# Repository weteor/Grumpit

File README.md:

### Grump'it

Grumpish 28 key BLE split keyboard 

## features

- Hotswap sockets (Choc V2)
- Seeed Xiao Controller (w/ ZMK firmware)
- gerber and case files (kicad files, stl as well as freecad files)
- Bluetooth (w/ Xiao BLE)
- completely open source, permissive license ([CERN-OHL-P](https://cern-ohl.web.cern.ch/home))

## want one?

All production files you need to build your own board can be found [here](./prod/).

The PCB is reversable, so you need two for a set.

Apart from pcbs and cases you need:

- 28 hotswap sockets

- 28 diodes (1N4148 int SOT-123)

- 28 of your favourite choc V2 low profile switches

- 2x Seeed Xiao BLE

- 2x LiPo rechargable batteries, 401230 110 mAh fit, you may be able to find others that fit. Max battery dimensions that should fit are 36x13x5mm

- a small piece (2-5 cm) of 1.75mm translucent filament as for the leds.

- 4x M2 heat inserts

- 4x M2 screws, around 8-9 mm should work.

- **optionally** 2x USB Connector C-Type, 12 pin/16pin, mid-mount (1.6mm)

To build just solder all components on one side of the PCB, make sure you don't do the same side twice. Diode direction is marked on the pcb. Solder the battery cable to the same side you mounted the components on and make sure you've got the polarity right.

For the case melt in the heat inserts. Cut off a small piece (so it fits in the groove in the bottom case) and push in into the hole. It should go in with little force.

Then just flash (and optionally change) the firmware and you should be ready to go.

### firmware

Config for ZMK can be found here: 
- [Github actions](https://github.com/weteor/grumpit-zmk-config)
- [local](./firmware).

Bootloader should be available on plugin until firmware is written. After flashing you may access the bootloader by double pressing the reset button.

### special thanks

[Forager](https://github.com/carrefinho/forager) for solving bottom mount Xiaos. I just plainly took his bottom case design for the reset button and led and copied it for this case. Such a great idea!

### the rest

Everything in this repository is free to use however you might see fit. If you want to support me and my projects, please consider linking back to this repository if you build/change/use anything.

If you would like to send me a tip, you could do it [here](https://ko-fi.com/weteor) (Please don't feel like you have to).

### more pictures

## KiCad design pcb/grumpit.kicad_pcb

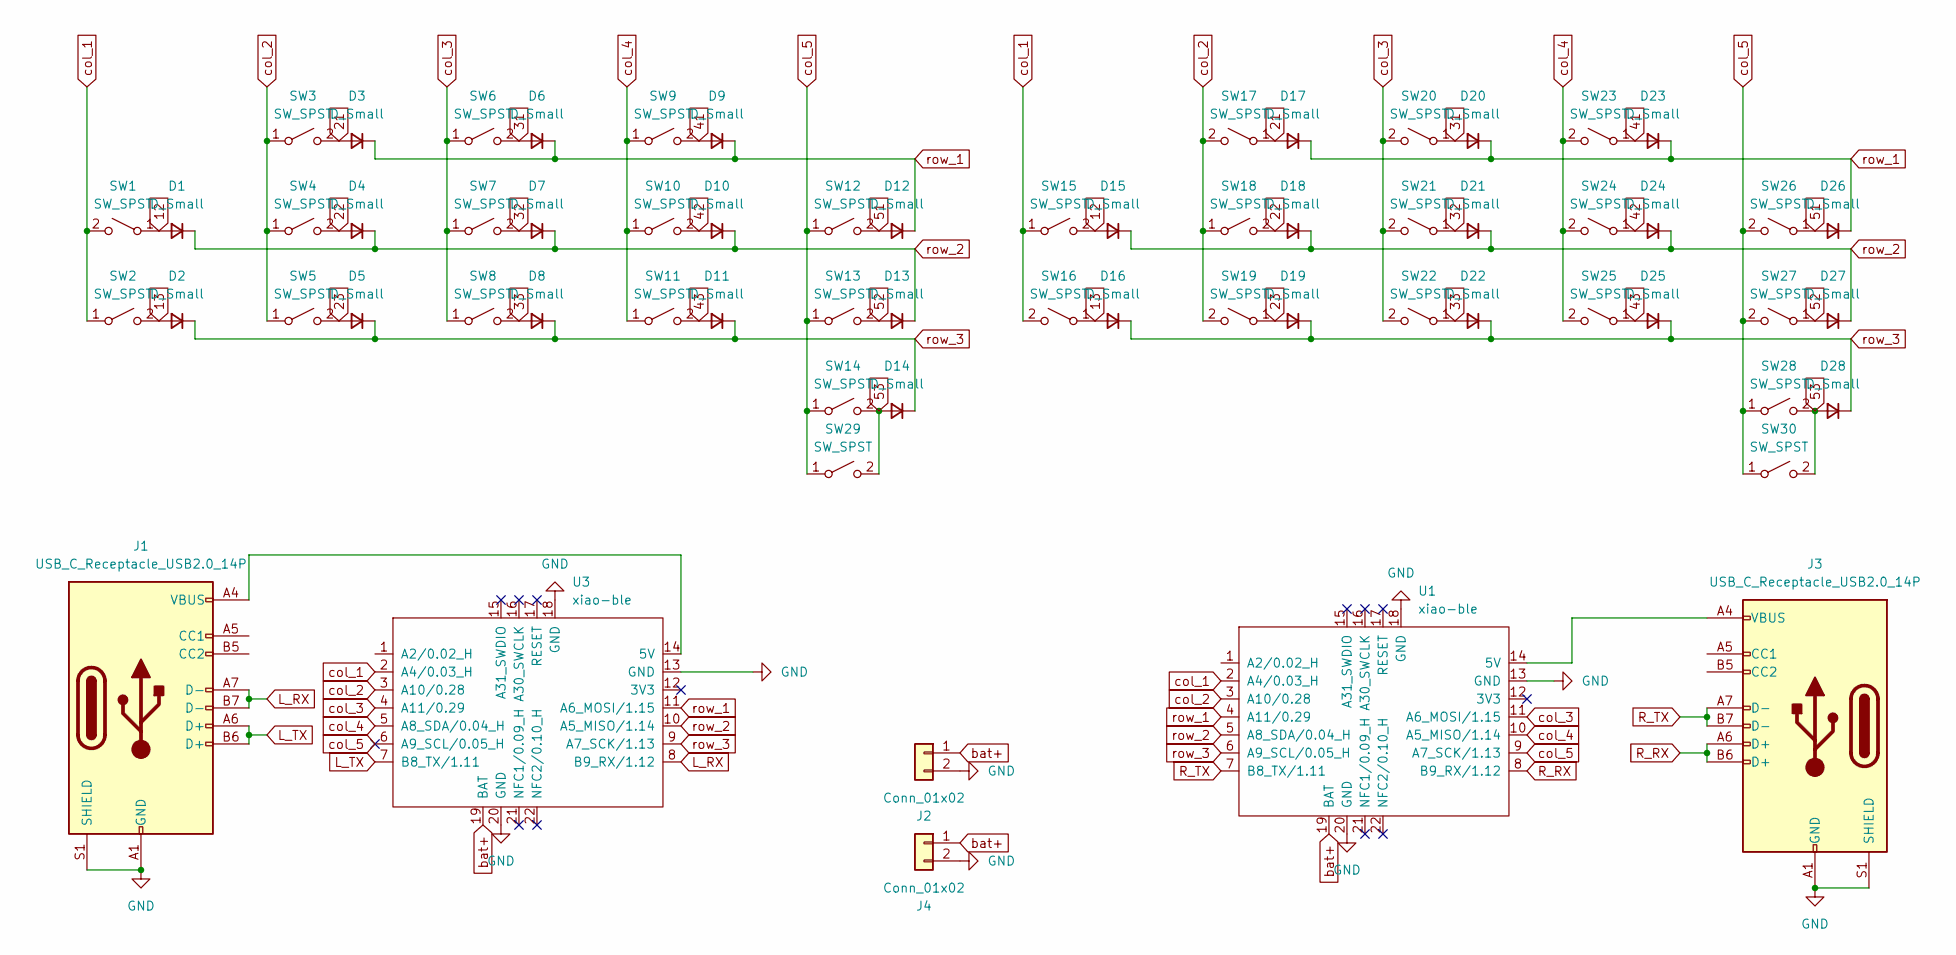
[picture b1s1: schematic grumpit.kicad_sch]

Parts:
D1, D2, D3, D4, D5, D6, D7, D8, D9, D10, D11, D12, D13, D14, D15, D16, D17, D18, D19, D20, D21, D22, D23, D24, D25, D26, D27, D28: D_Small; D_SOD-123
J1, J3: USB_C_Receptacle_USB2.0_14P; USB-C-12-Pin-MidMount
J2, J4: Conn_01x02; battery_pads
SW1, SW2, SW3, SW4, SW5, SW6, SW7, SW8, SW9, SW10, SW11, SW12, SW13, SW15, SW16, SW17, SW18, SW19, SW20, SW21, SW22, SW23, SW24, SW25, SW26, SW27: SW_SPST; ChocV2_HS_1u
SW14, SW28: SW_SPST; ChocV2_HS_1.5u
SW29, SW30: SW_SPST; ChocV2_HS_1.25u
U1, U3: xiao-ble; xiao-ble-smd_upside_down

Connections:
12: D1.2 (A), D15.2 (A), SW1.1 (A), SW15.2 (B)
13: D2.2 (A), D16.2 (A), SW2.2 (B), SW16.1 (A)
21: D3.2 (A), D17.2 (A), SW3.2 (B), SW17.1 (A)
22: D4.2 (A), D18.2 (A), SW4.2 (B), SW18.2 (B)
23: D5.2 (A), D19.2 (A), SW5.2 (B), SW19.1 (A)
31: D6.2 (A), D20.2 (A), SW6.2 (B), SW20.1 (A)
32: D7.2 (A), D21.2 (A), SW7.2 (B), SW21.1 (A)
33: D8.2 (A), D22.2 (A), SW8.2 (B), SW22.1 (A)
41: D9.2 (A), D23.2 (A), SW9.2 (B), SW23.1 (A)
42: D10.2 (A), D24.2 (A), SW10.2 (B), SW24.1 (A)
43: D11.2 (A), D25.2 (A), SW11.2 (B), SW25.1 (A)
51: D12.2 (A), D26.2 (A), SW12.2 (B), SW26.1 (A)
52: D13.2 (A), D27.2 (A), SW13.2 (B), SW27.1 (A)
53: D14.2 (A), D28.2 (A), SW14.2 (B), SW28.2 (B), SW29.2 (B), SW30.2 (B)
GND: J1.A1 (GND), J1.A12 (GND), J1.B1 (GND), J1.B12 (GND), J1.S1 (SHIELD), J2.2, J3.A1 (GND), J3.A12 (GND), J3.B1 (GND), J3.B12 (GND), J3.S1 (SHIELD), J4.2, U1.13 (GND), U1.18 (GND), U1.20 (GND), U3.13 (GND), U3.18 (GND), U3.20 (GND)
L_RX: J1.A7 (D-), J1.B7 (D-), U3.8 (B9_RX/1.12)
L_TX: J1.A6 (D+), J1.B6 (D+), U3.7 (B8_TX/1.11)
unnamed: J3.A4 (VBUS), J3.A9 (VBUS), J3.B4 (VBUS), J3.B9 (VBUS), U1.14 (5V)
unnamed: J1.A4 (VBUS), J1.A9 (VBUS), J1.B4 (VBUS), J1.B9 (VBUS), U3.14 (5V)
R_RX: J3.A6 (D+), J3.B6 (D+), U1.8 (B9_RX/1.12)
R_TX: J3.A7 (D-), J3.B7 (D-), U1.7 (B8_TX/1.11)
bat+: J2.1, J4.1, U1.19 (BAT), U3.19 (BAT)
col_1: SW1.2 (B), SW2.1 (A), SW15.1 (A), SW16.2 (B), U1.2 (A4/0.03_H), U3.2 (A4/0.03_H)
col_2: SW3.1 (A), SW4.1 (A), SW5.1 (A), SW17.2 (B), SW18.1 (A), SW19.2 (B), U1.3 (A10/0.28), U3.3 (A10/0.28)
col_3: SW6.1 (A), SW7.1 (A), SW8.1 (A), SW20.2 (B), SW21.2 (B), SW22.2 (B), U1.11 (A6_MOSI/1.15), U3.4 (A11/0.29)
col_4: SW9.1 (A), SW10.1 (A), SW11.1 (A), SW23.2 (B), SW24.2 (B), SW25.2 (B), U1.10 (A5_MISO/1.14), U3.5 (A8_SDA/0.04_H)
col_5: SW12.1 (A), SW13.1 (A), SW14.1 (A), SW26.2 (B), SW27.2 (B), SW28.1 (A), SW29.1 (A), SW30.1 (A), U1.9 (A7_SCK/1.13), U3.6 (A9_SCL/0.05_H)
row_1: D3.1 (K), D6.1 (K), D9.1 (K), D12.1 (K), D17.1 (K), D20.1 (K), D23.1 (K), D26.1 (K), U1.4 (A11/0.29), U3.11 (A6_MOSI/1.15)
row_2: D1.1 (K), D4.1 (K), D7.1 (K), D10.1 (K), D13.1 (K), D15.1 (K), D18.1 (K), D21.1 (K), D24.1 (K), D27.1 (K), U1.5 (A8_SDA/0.04_H), U3.10 (A5_MISO/1.14)
row_3: D2.1 (K), D5.1 (K), D8.1 (K), D11.1 (K), D14.1 (K), D16.1 (K), D19.1 (K), D22.1 (K), D25.1 (K), D28.1 (K), U1.6 (A9_SCL/0.05_H), U3.9 (A7_SCK/1.13)

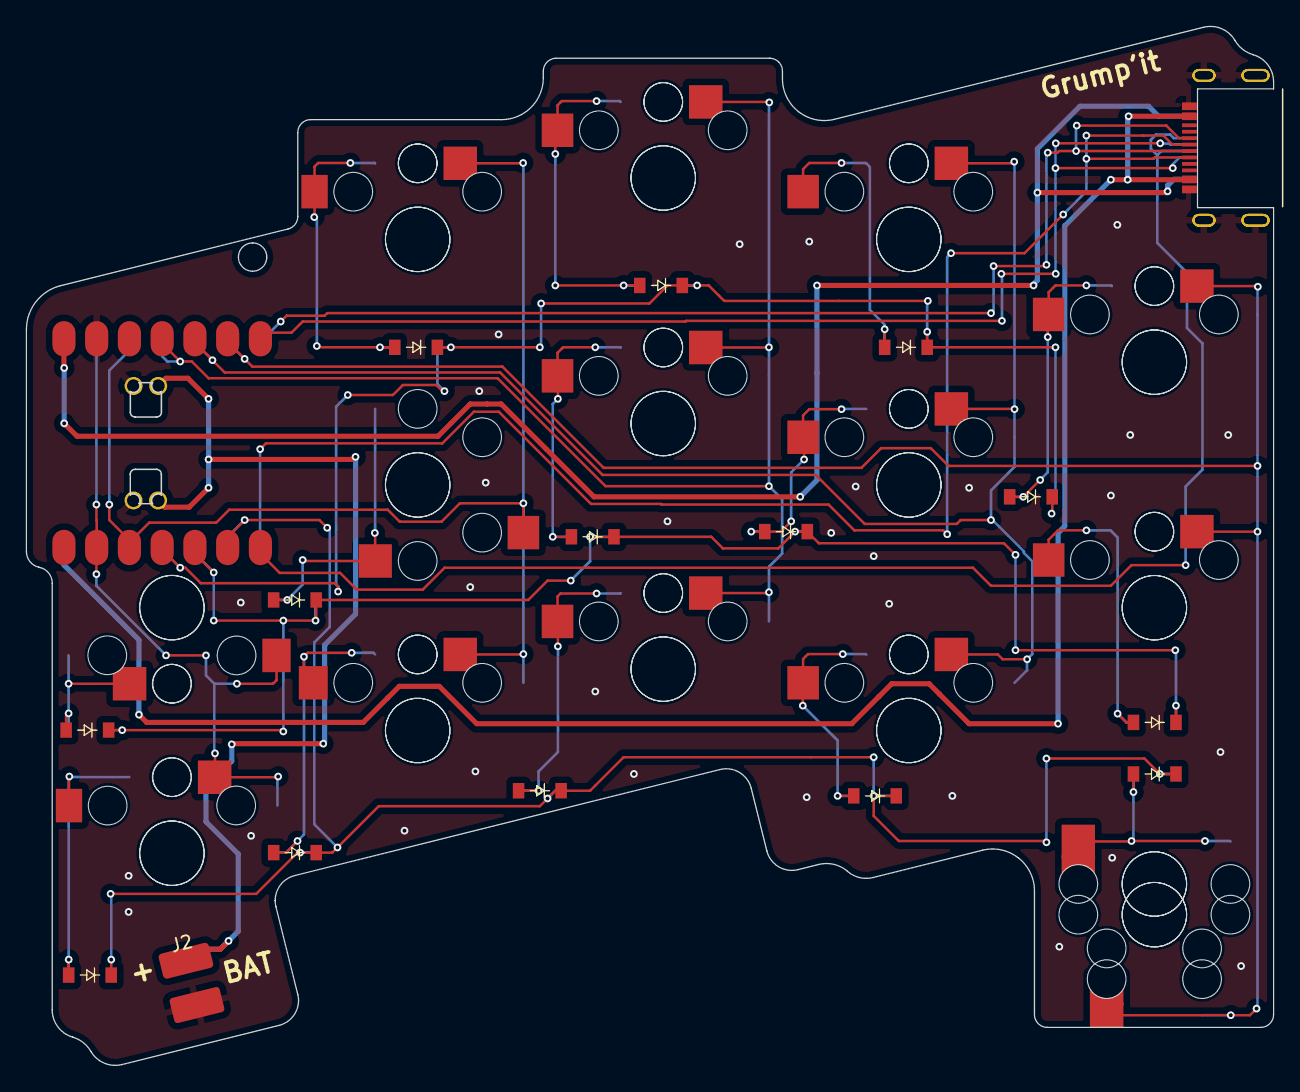
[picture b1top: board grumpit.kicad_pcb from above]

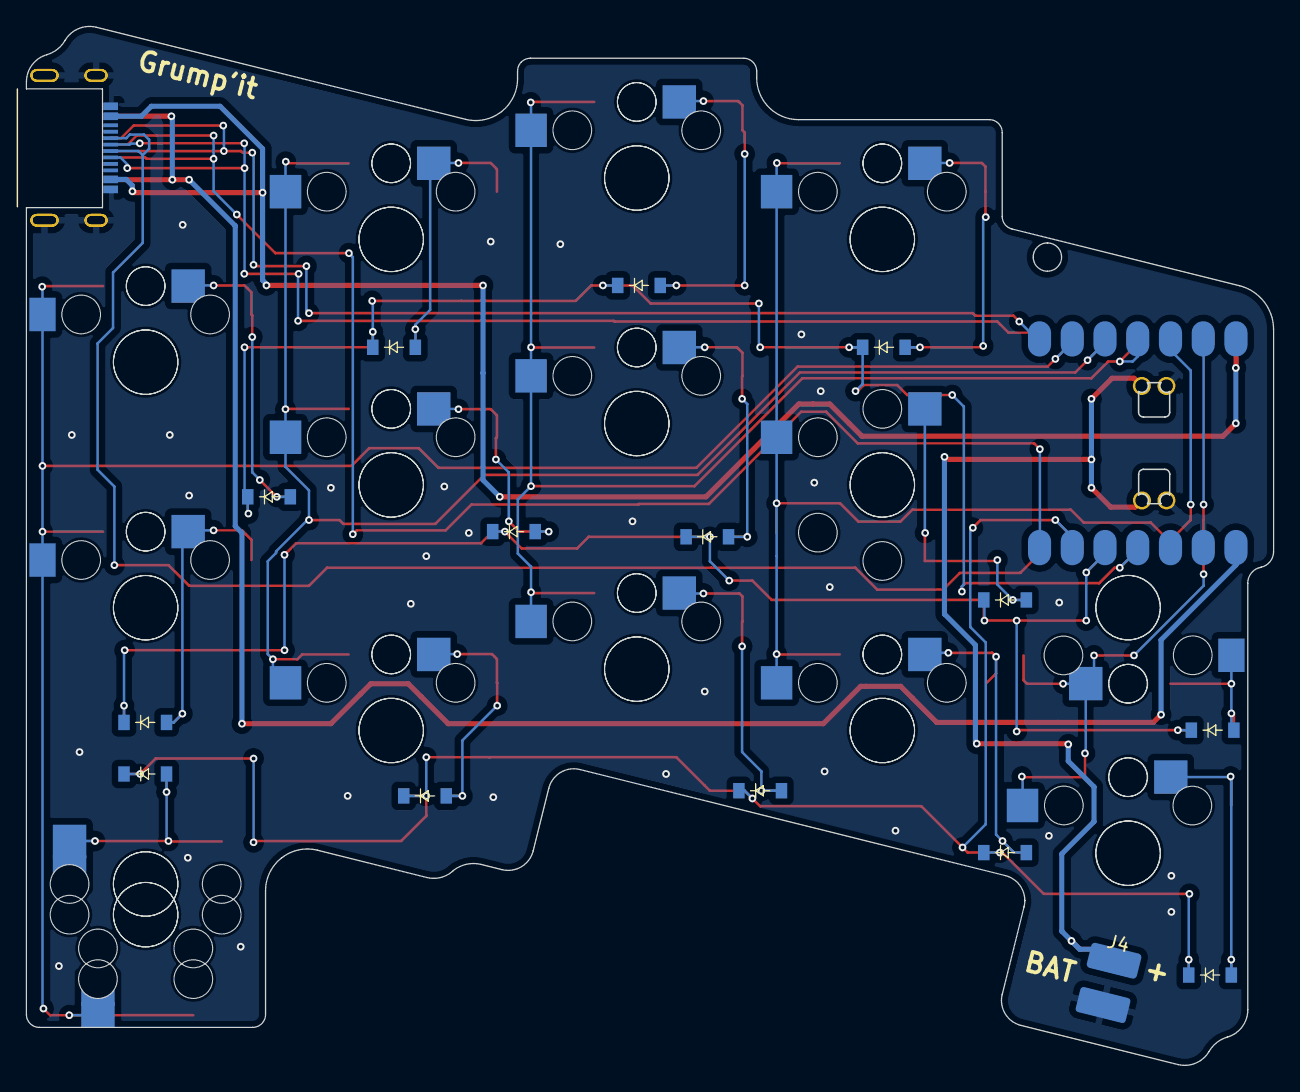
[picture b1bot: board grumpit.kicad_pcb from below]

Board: 2 copper layers, 96.7 x 80.6 mm, 64 parts (32 on the bottom side), 30 nets.

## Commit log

2026-02-23 initial add pcb
2026-02-23 initial add case
2026-02-23 add production files
2026-02-23 add firmware
2026-02-23 add license
2026-02-23 add images
2026-02-23 add github actions firmware build instructions
